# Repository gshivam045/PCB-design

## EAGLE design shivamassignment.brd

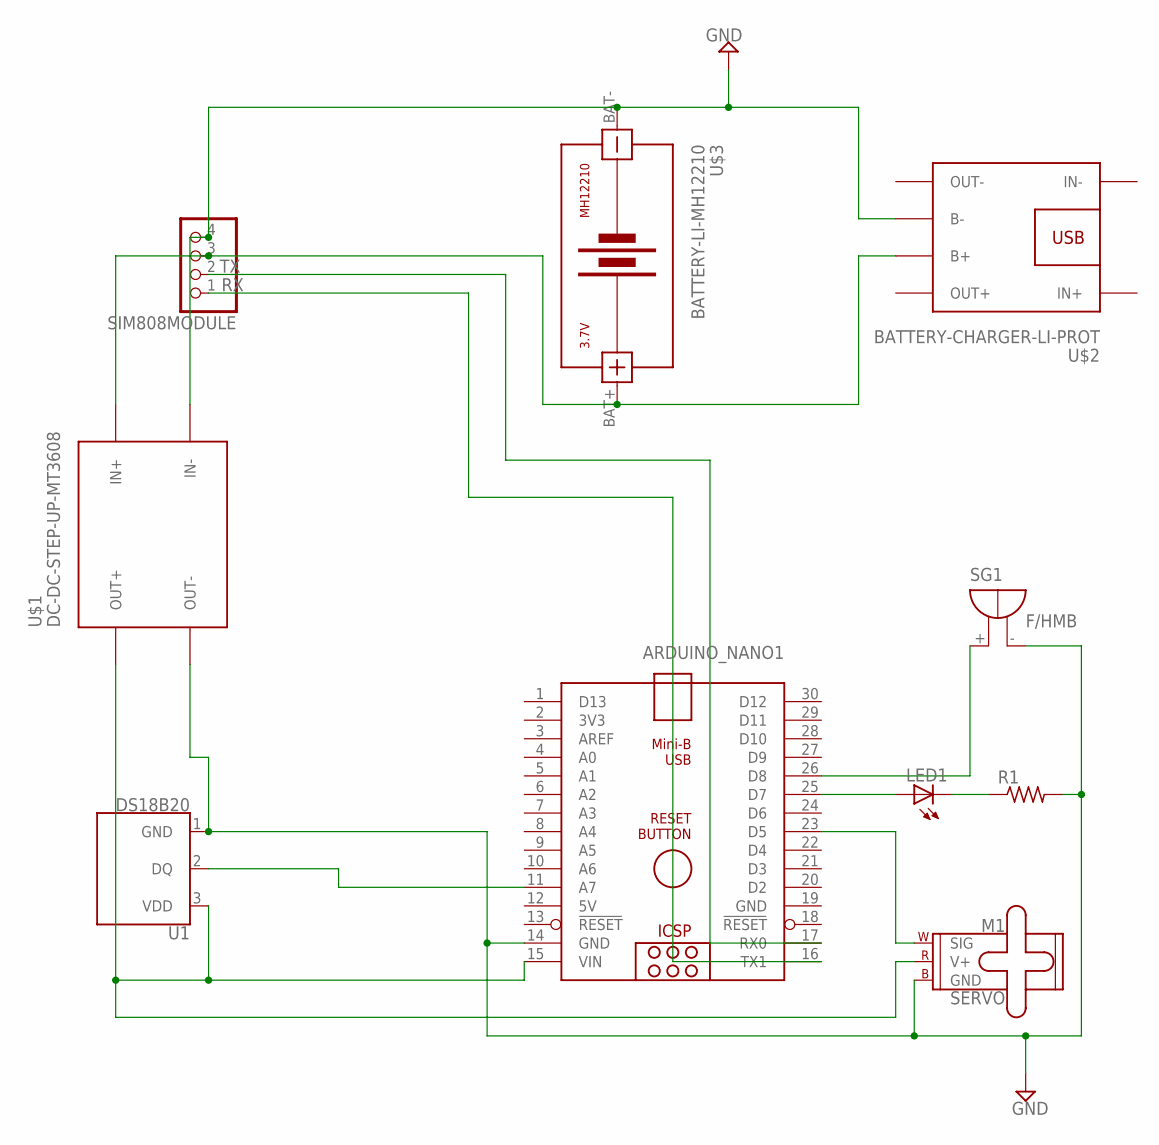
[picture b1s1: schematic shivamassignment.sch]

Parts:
ARDUINO_NANO1: ARDUINO_NANO
LED1: LED5MM
M1: SERVO; 1X03
R1: R-US_0204/7; 0204/7
SG1: F/HMB
SIM808MODULE: PINHD-1X4; 1X04
U1: DS18B20; TO-92-AMMO
U$1: DC-DC-STEP-UP-MT3608
U$2: BATTERY-CHARGER-LI-PROT
U$3: BATTERY-LI-MH12210

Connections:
5V: ARDUINO_NANO1.12 (5V)
GND: ARDUINO_NANO1.14 (GND), ARDUINO_NANO1.19 (GND), M1.3 (GND), R1.2, SG1.-, SIM808MODULE.4, U1.1 (GND), U$1.IN-, U$1.OUT-, U$2.B-, U$3.BAT-
unnamed: SIM808MODULE.3, U$1.IN+, U$2.B+, U$3.BAT+
unnamed: ARDUINO_NANO1.15 (VIN), M1.2 (V+), U1.3 (VDD), U$1.OUT+
unnamed: ARDUINO_NANO1.11 (A7), U1.2 (DQ)
unnamed: ARDUINO_NANO1.25 (D7), LED1.A
unnamed: LED1.K (C), R1.1
unnamed: ARDUINO_NANO1.26 (D8), SG1.+
unnamed: ARDUINO_NANO1.23 (D5), M1.1 (SIG)
RX: ARDUINO_NANO1.16 (TX1), SIM808MODULE.1
TX: ARDUINO_NANO1.17 (RX0), SIM808MODULE.2

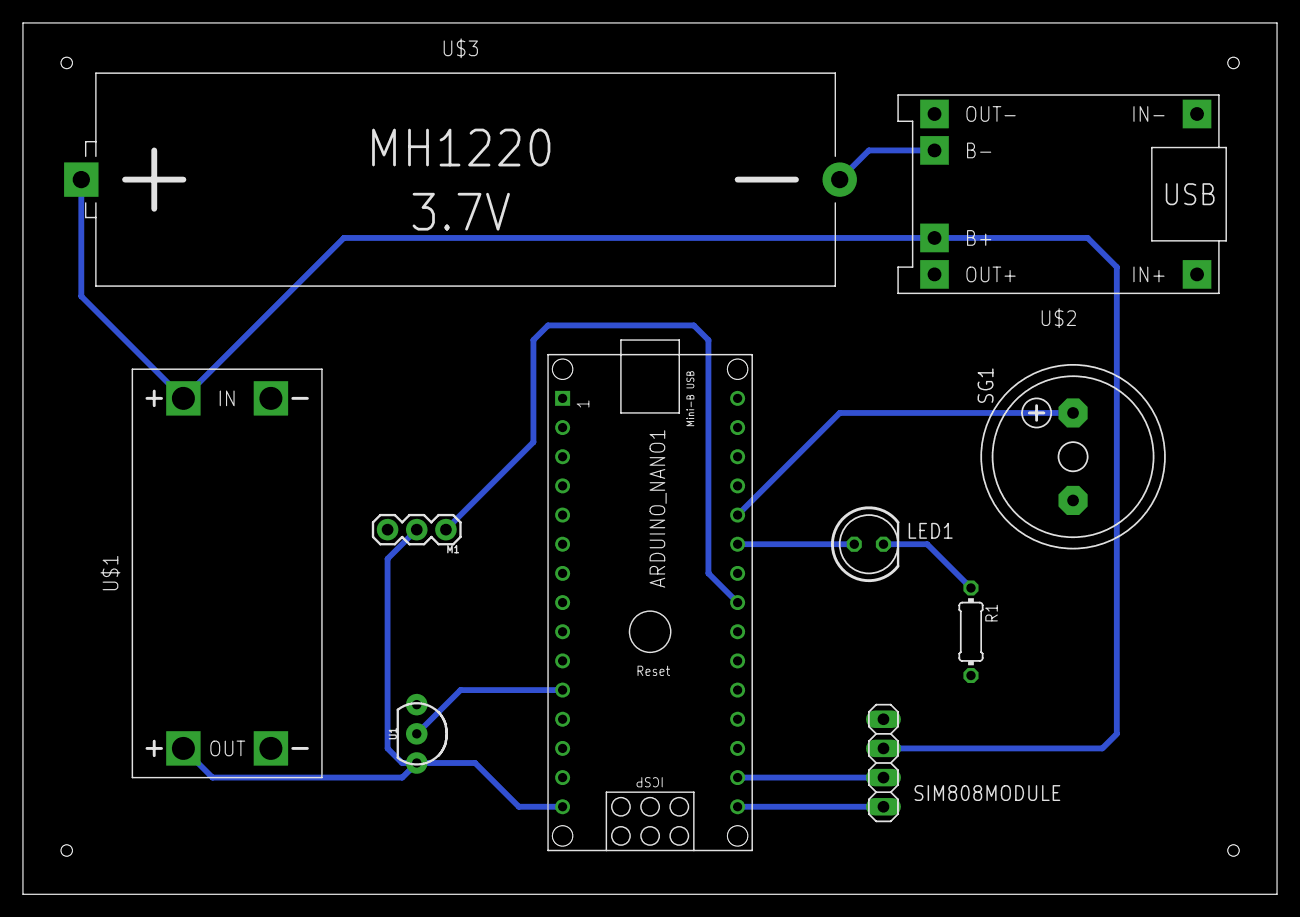
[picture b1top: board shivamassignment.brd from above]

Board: 2 copper layers, 109.2 x 75.9 mm, 10 parts (0 on the bottom side), 10 nets.

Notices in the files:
parts and their libraries:
SparkFun-Electromechanical: Licensing: Creative Commons ShareAlike 4.0 International - https://creativecommons.org/licenses/by-sa/4.0
diy-modules: Released under the Creative Commons Attribution 4.0 International License: http://creativecommons.org/licenses/by/4.0
